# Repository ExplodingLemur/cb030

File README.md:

# cb030
4-layer redesign of the [CB030](https://www.retrobrewcomputers.org/doku.php?id=builderpages:plasmo:cb030) homebrew computer by plasmo on retrobrewcomputers.org.

Specifically based on the [16-bit CF interface variant rev1](https://www.retrobrewcomputers.org/doku.php?id=builderpages:plasmo:cb030:cb030_rev1:16-bit_cf_upgrade)

Requires [these KiCAD library files](https://github.com/ExplodingLemur/kicad_libs)

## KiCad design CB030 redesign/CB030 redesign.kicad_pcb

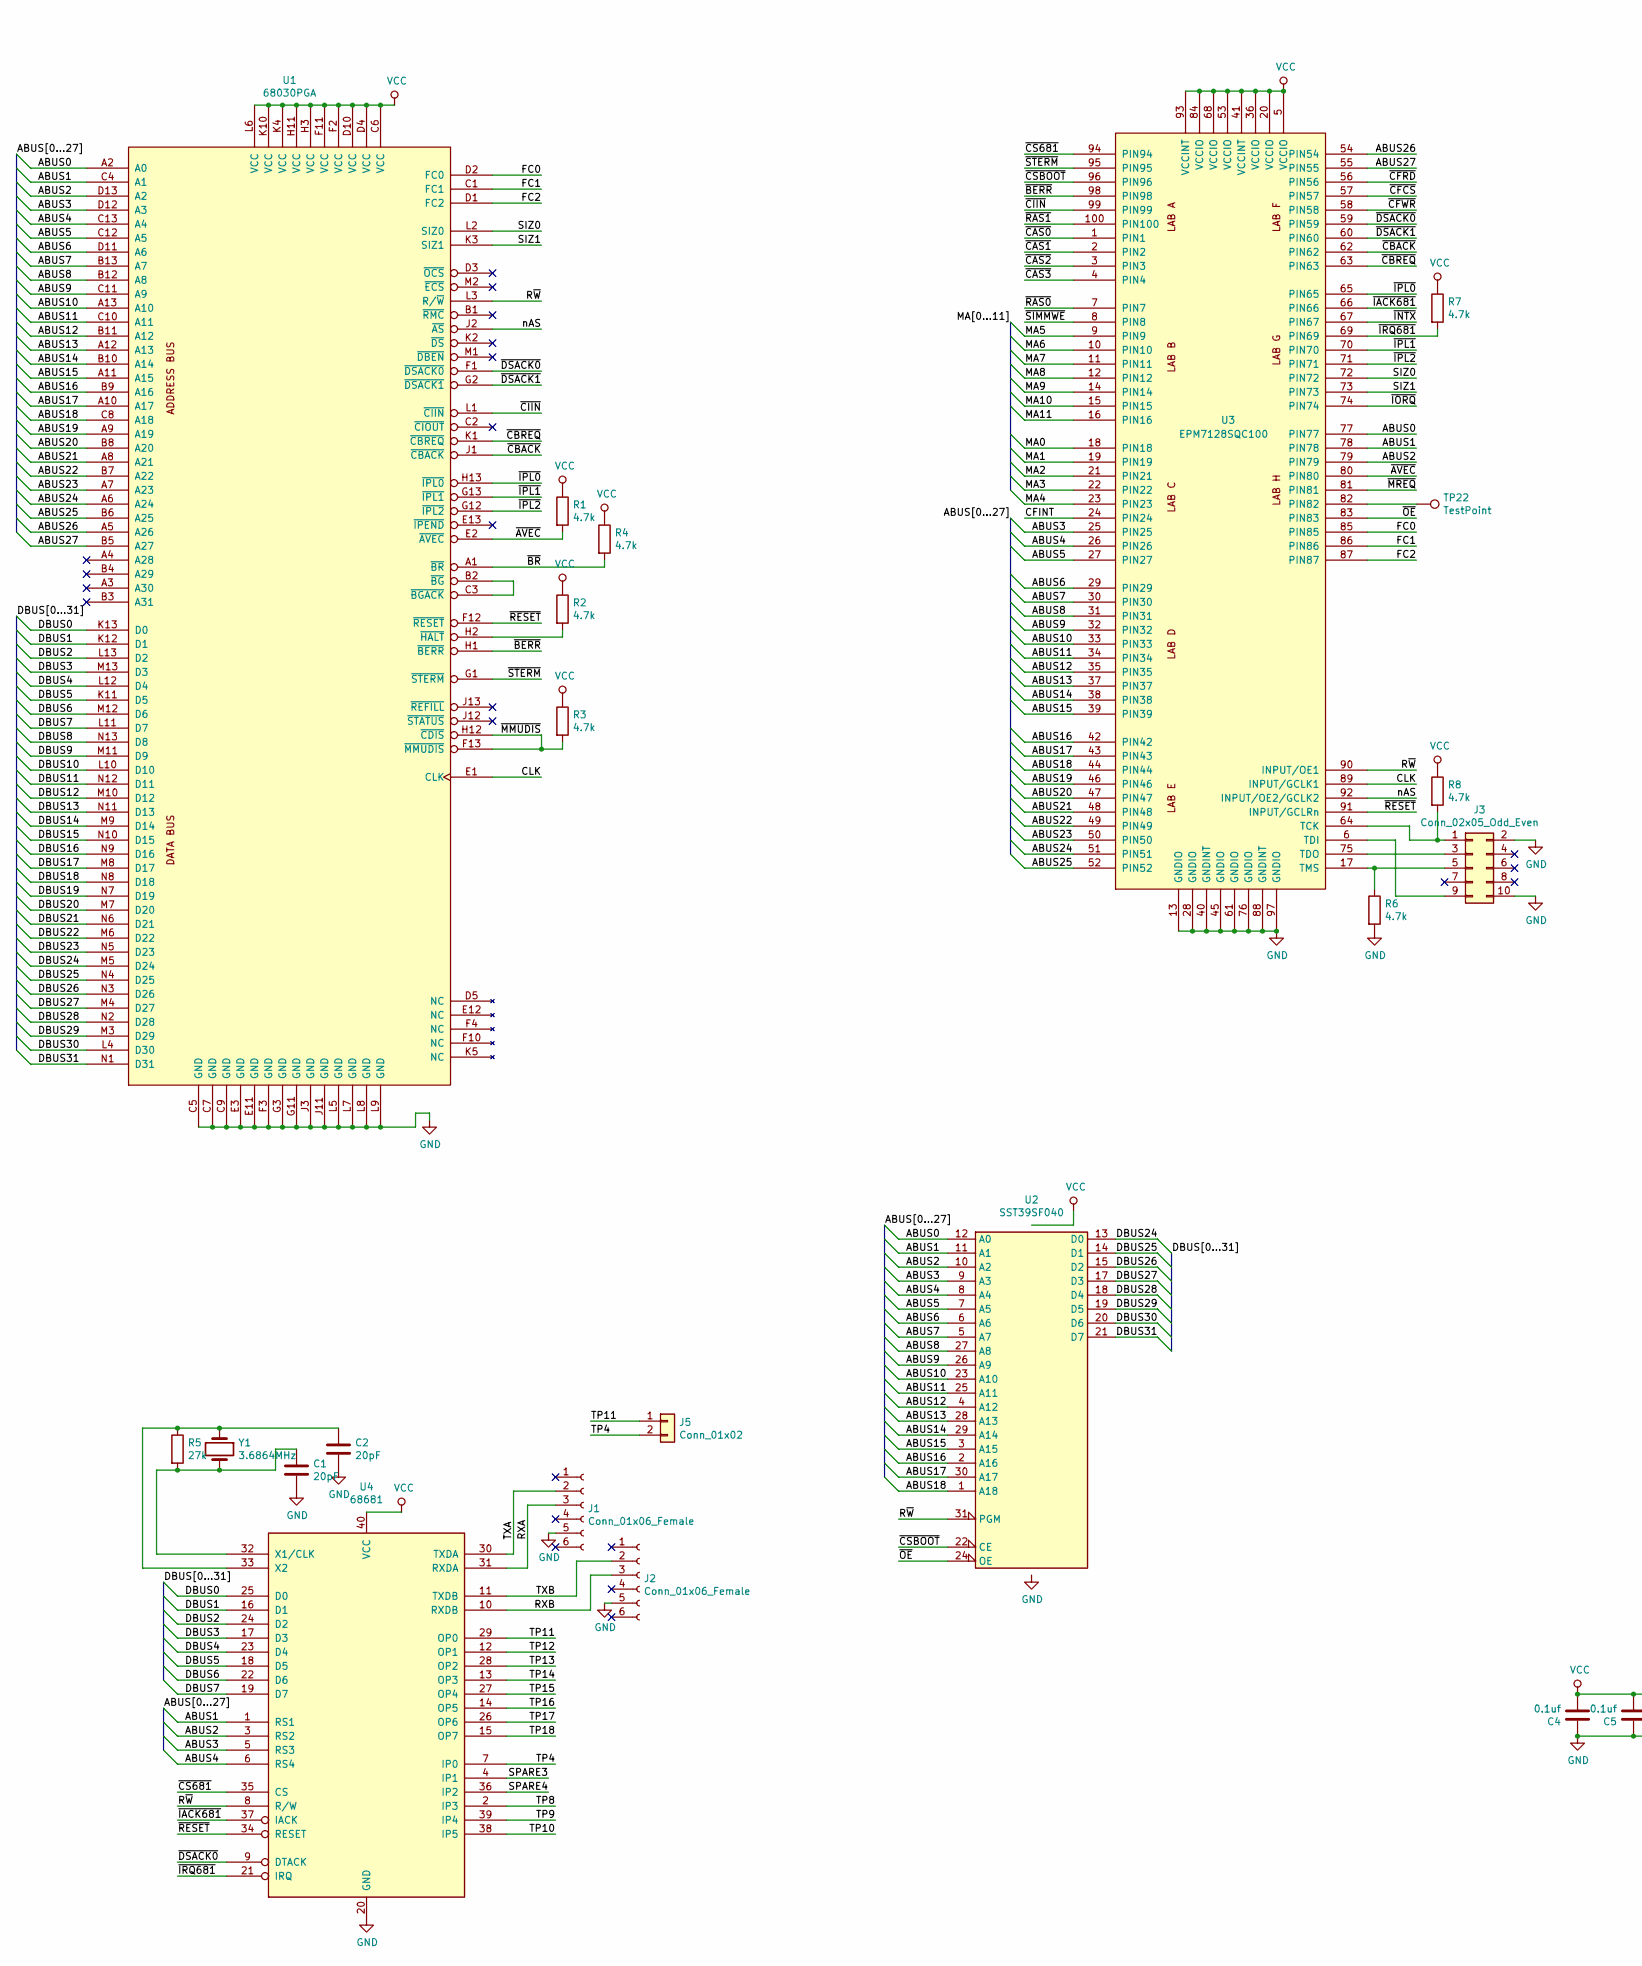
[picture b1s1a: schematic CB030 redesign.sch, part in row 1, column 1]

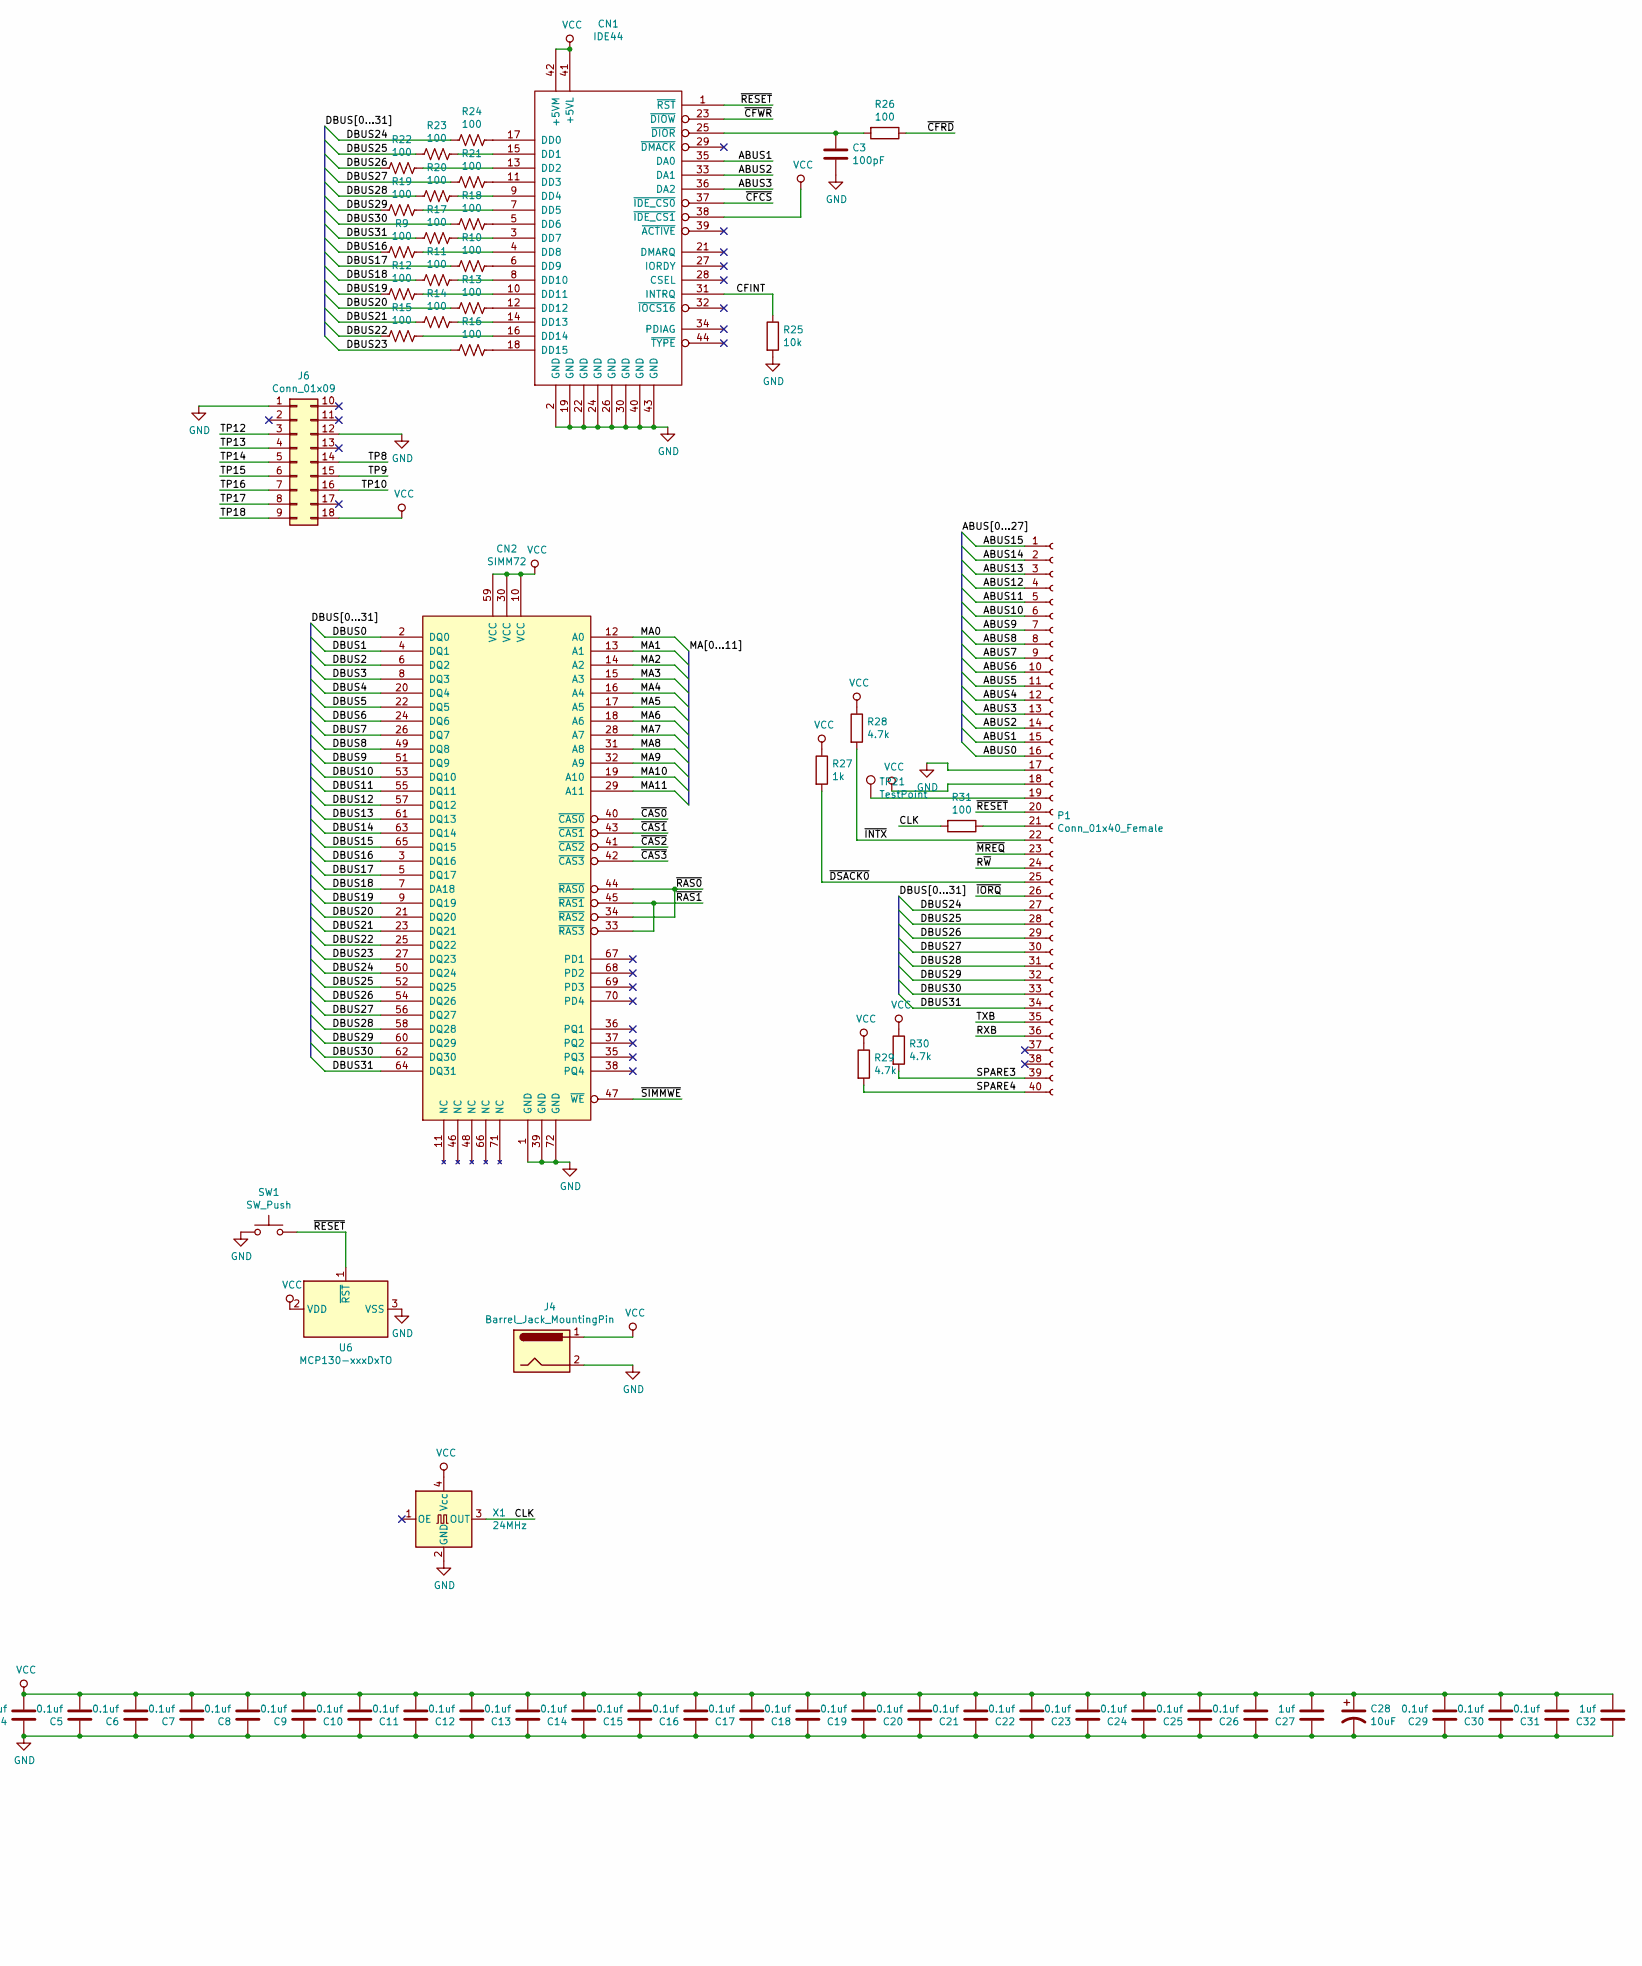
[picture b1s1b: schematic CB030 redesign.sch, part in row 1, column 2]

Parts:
C1, C2: 20pF; C_0805_2012Metric_Pad1.15x1.40mm_HandSolder
C3: 100pF; C_0805_2012Metric_Pad1.15x1.40mm_HandSolder
C4, C5, C6, C7, C8, C9, C10, C11, C12, C13, C14, C15, C16, C17, C18, C19, C20, C21, C22, C23, C24, C25, C26, C29, C30, C31: 0.1uf; C_0805_2012Metric_Pad1.15x1.40mm_HandSolder
C27, C32: 1uf; C_0805_2012Metric_Pad1.15x1.40mm_HandSolder
C28: 10uF; CP_Elec_4x5.8
CN1: IDE44; PinHeader_2x22_P2.00mm_Vertical
CN2: SIMM72; SIMM 72POS LEFT
J1: Conn_01x06_Female; PinSocket_1x06_P2.54mm_Vertical
J2: Conn_01x06_Female; PinSocket_1x06_P2.54mm_Horizontal
J3: Conn_02x05_Odd_Even; PinHeader_2x05_P2.54mm_Vertical
J4: Barrel_Jack_MountingPin; BarrelJack_Horizontal
J5: Conn_01x02; PinHeader_1x02_P2.54mm_Vertical
J6: Conn_01x09; PinHeader_2x09_P2.54mm_Vertical
P1: Conn_01x40_Female; PinSocket_1x40_P2.54mm_Vertical
R1, R2, R3, R4, R6, R7, R8, R28, R29, R30: 4.7k; R_0805_2012Metric_Pad1.15x1.40mm_HandSolder
R5: 27k; R_0805_2012Metric_Pad1.15x1.40mm_HandSolder
R9, R10, R11, R12, R13, R14, R15, R16, R17, R18, R19, R20, R21, R22, R23, R24, R26, R31: 100; R_0805_2012Metric_Pad1.15x1.40mm_HandSolder
R25: 10k; R_0805_2012Metric_Pad1.15x1.40mm_HandSolder
R27: 1k; R_0805_2012Metric_Pad1.15x1.40mm_HandSolder
SW1: SW_Push; SW_PUSH_6mm
TP21, TP22: TestPoint; TestPoint_THTPad_D1.5mm_Drill0.7mm
U1: 68030PGA; MC68030-RC
U2: SST39SF040; DIP-32_W15.24mm_Socket
U3: EPM7128SQC100; PQFP-100_14x20mm_P0.65mm
U4: 68681; DIP-40_W15.24mm_Socket
U6: MCP130-xxxDxTO; TO-92_Inline
X1: 24MHz; Oscillator_SMD_SeikoEpson_SG8002CA-4Pin_7.0x5.0mm_HandSolde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; Part SG7050CCN 24.000000M-HJGA3
Y1: 3.6864MHz; Crystal_SMD_HC49-SD_HandSoldering; Part ABLS-3.6864MHZ-20-B-3-H-T

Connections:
/ABUS0: P1.16, U1.A2 (A0), U2.12 (A0), U3.77 (PIN77)
/ABUS1: CN1.35 (DA0), P1.15, U1.C4 (A1), U2.11 (A1), U3.78 (PIN78), U4.1 (RS1)
/ABUS2: CN1.33 (DA1), P1.14, U1.D13 (A2), U2.10 (A2), U3.79 (PIN79), U4.3 (RS2)
/ABUS3: CN1.36 (DA2), P1.13, U1.D12 (A3), U2.9 (A3), U3.25 (PIN25), U4.5 (RS3)
/ABUS4: P1.12, U1.C13 (A4), U2.8 (A4), U3.26 (PIN26), U4.6 (RS4)
/ABUS5: P1.11, U1.C12 (A5), U2.7 (A5), U3.27 (PIN27)
/ABUS6: P1.10, U1.D11 (A6), U2.6 (A6), U3.29 (PIN29)
/ABUS7: P1.9, U1.B13 (A7), U2.5 (A7), U3.30 (PIN30)
/ABUS8: P1.8, U1.B12 (A8), U2.27 (A8), U3.31 (PIN31)
/ABUS9: P1.7, U1.C11 (A9), U2.26 (A9), U3.32 (PIN32)
/ABUS10: P1.6, U1.A13 (A10), U2.23 (A10), U3.33 (PIN33)
/ABUS11: P1.5, U1.C10 (A11), U2.25 (A11), U3.34 (PIN34)
/ABUS12: P1.4, U1.B11 (A12), U2.4 (A12), U3.35 (PIN35)
/ABUS13: P1.3, U1.A12 (A13), U2.28 (A13), U3.37 (PIN37)
/ABUS14: P1.2, U1.B10 (A14), U2.29 (A14), U3.38 (PIN38)
/ABUS15: P1.1, U1.A11 (A15), U2.3 (A15), U3.39 (PIN39)
/ABUS16: U1.B9 (A16), U2.2 (A16), U3.42 (PIN42)
/ABUS17: U1.A10 (A17), U2.30 (A17), U3.43 (PIN43)
/ABUS18: U1.C8 (A18), U2.1 (A18), U3.44 (PIN44)
/ABUS19: U1.A9 (A19), U3.46 (PIN46)
/ABUS20: U1.B8 (A20), U3.47 (PIN47)
/ABUS21: U1.A8 (A21), U3.48 (PIN48)
/ABUS22: U1.B7 (A22), U3.49 (PIN49)
/ABUS23: U1.A7 (A23), U3.50 (PIN50)
/ABUS24: U1.A6 (A24), U3.51 (PIN51)
/ABUS25: U1.B6 (A25), U3.52 (PIN52)
/ABUS26: U1.A5 (A26), U3.54 (PIN54)
/ABUS27: U1.B5 (A27), U3.55 (PIN55)
/CFINT: CN1.31 (INTRQ), R25.1, U3.24 (PIN24)
/CLK: R31.2, U1.E1 (CLK), U3.89 (INPUT/GCLK1), X1.3 (OUT)
/DBUS0: CN2.2 (DQ0), U1.K13 (D0), U4.25 (D0)
/DBUS1: CN2.4 (DQ1), U1.K12 (D1), U4.16 (D1)
/DBUS2: CN2.6 (DQ2), U1.L13 (D2), U4.24 (D2)
/DBUS3: CN2.8 (DQ3), U1.M13 (D3), U4.17 (D3)
/DBUS4: CN2.20 (DQ4), U1.L12 (D4), U4.23 (D4)
/DBUS5: CN2.22 (DQ5), U1.K11 (D5), U4.18 (D5)
/DBUS6: CN2.24 (DQ6), U1.M12 (D6), U4.22 (D6)
/DBUS7: CN2.26 (DQ7), U1.L11 (D7), U4.19 (D7)
/DBUS8: CN2.49 (DQ8), U1.N13 (D8)
/DBUS9: CN2.51 (DQ9), U1.M11 (D9)
/DBUS10: CN2.53 (DQ10), U1.L10 (D10)
/DBUS11: CN2.55 (DQ11), U1.N12 (D11)
/DBUS12: CN2.57 (DQ12), U1.M10 (D12)
/DBUS13: CN2.61 (DQ13), U1.N11 (D13)
/DBUS14: CN2.63 (DQ14), U1.M9 (D14)
/DBUS15: CN2.65 (DQ15), U1.N10 (D15)
/DBUS16: CN2.3 (DQ16), R9.2, U1.N9 (D16)
/DBUS17: CN2.5 (DQ17), R10.2, U1.M8 (D17)
/DBUS18: CN2.7 (DA18), R11.2, U1.N8 (D18)
/DBUS19: CN2.9 (DQ19), R12.2, U1.N7 (D19)
/DBUS20: CN2.21 (DQ20), R13.2, U1.M7 (D20)
/DBUS21: CN2.23 (DQ21), R14.2, U1.N6 (D21)
/DBUS22: CN2.25 (DQ22), R15.2, U1.M6 (D22)
/DBUS23: CN2.27 (DQ23), R16.2, U1.N5 (D23)
/DBUS24: CN2.50 (DQ24), P1.27, R24.2, U1.M5 (D24), U2.13 (D0)
/DBUS25: CN2.52 (DQ25), P1.28, R23.2, U1.N4 (D25), U2.14 (D1)
/DBUS26: CN2.54 (DQ26), P1.29, R22.2, U1.N3 (D26), U2.15 (D2)
/DBUS27: CN2.56 (DQ27), P1.30, R21.2, U1.M4 (D27), U2.17 (D3)
/DBUS28: CN2.58 (DQ28), P1.31, R20.2, U1.N2 (D28), U2.18 (D4)
/DBUS29: CN2.60 (DQ29), P1.32, R19.2, U1.M3 (D29), U2.19 (D5)
/DBUS30: CN2.62 (DQ30), P1.33, R18.2, U1.L4 (D30), U2.20 (D6)
/DBUS31: CN2.64 (DQ31), P1.34, R17.2, U1.N1 (D31), U2.21 (D7)
/FC0: U1.D2 (FC0), U3.85 (PIN85)
/FC1: U1.C1 (FC1), U3.86 (PIN86)
/FC2: U1.D1 (FC2), U3.87 (PIN87)
/MA0: CN2.12 (A0), U3.18 (PIN18)
/MA1: CN2.13 (A1), U3.19 (PIN19)
/MA2: CN2.14 (A2), U3.21 (PIN21)
/MA3: CN2.15 (A3), U3.22 (PIN22)
/MA4: CN2.16 (A4), U3.23 (PIN23)
/MA5: CN2.17 (A5), U3.9 (PIN9)
/MA6: CN2.18 (A6), U3.10 (PIN10)
/MA7: CN2.28 (A7), U3.11 (PIN11)
/MA8: CN2.31 (A8), U3.12 (PIN12)
/MA9: CN2.32 (A9), U3.14 (PIN14)
/MA10: CN2.19 (A10), U3.15 (PIN15)
/MA11: CN2.29 (A11), U3.16 (PIN16)
/RXA: J1.3, U4.31 (RXDA)
/RXB: J2.3, P1.36, U4.10 (RXDB)
/R~W: P1.24, U1.L3 (R/~W), U2.31 (PGM), U3.90 (INPUT/OE1), U4.8 (R/W)
/SIZ0: U1.L2 (SIZ0), U3.72 (PIN72)
/SIZ1: U1.K3 (SIZ1), U3.73 (PIN73)
/SPARE3: P1.39, R30.2, U4.4 (IP1)
/SPARE4: P1.40, R29.2, U4.36 (IP2)
/TP4: J5.2, U4.7 (IP0)
/TP8: J6.14, U4.2 (IP3)
/TP9: J6.15, U4.39 (IP4)
/TP10: J6.16, U4.38 (IP5)
/TP11: J5.1, U4.29 (OP0)
/TP12: J6.3, U4.12 (OP1)
/TP13: J6.4, U4.28 (OP2)
/TP14: J6.5, U4.13 (OP3)
/TP15: J6.6, U4.27 (OP4)
/TP16: J6.7, U4.14 (OP5)
/TP17: J6.8, U4.26 (OP6)
/TP18: J6.9, U4.15 (OP7)
/TXA: J1.2, U4.30 (TXDA)
/TXB: J2.2, P1.35, U4.11 (TXDB)
/nAS: U1.J2 (~AS), U3.92 (INPUT/OE2/GCLK2)
/~AVEC: R1.2, U1.E2 (~AVEC), U3.80 (PIN80)
/~BERR: U1.H1 (~BERR), U3.98 (PIN98)
/~BR: R4.2, U1.A1 (~BR)
/~CAS0: CN2.40 (~CAS0), U3.1 (PIN1)
/~CAS1: CN2.43 (~CAS1), U3.2 (PIN2)
/~CAS2: CN2.41 (~CAS2), U3.3 (PIN3)
/~CAS3: CN2.42 (~CAS3), U3.4 (PIN4)
/~CBACK: U1.J1 (~CBACK), U3.62 (PIN62)
/~CBREQ: U1.K1 (~CBREQ), U3.63 (PIN63)
/~CFCS: CN1.37 (~IDE_CS0), U3.57 (PIN57)
/~CFRD: R26.1, U3.56 (PIN56)
/~CFWR: CN1.23 (~DIOW), U3.58 (PIN58)
/~CIIN: U1.L1 (~CIIN), U3.99 (PIN99)
/~CS681: U3.94 (PIN94), U4.35 (CS)
/~CSBOOT: U2.22 (CE), U3.96 (PIN96)
/~DSACK0: P1.25, R27.2, U1.F1 (~DSACK0), U3.59 (PIN59), U4.9 (DTACK)
/~DSACK1: U1.G2 (~DSACK1), U3.60 (PIN60)
/~IACK681: U3.66 (PIN66), U4.37 (IACK)
/~INTX: P1.22, R28.2, U3.67 (PIN67)
/~IORQ: P1.26, U3.74 (PIN74)
/~IPL0: U1.H13 (~IPL0), U3.65 (PIN65)
/~IPL1: U1.G13 (~IPL1), U3.70 (PIN70)
/~IPL2: U1.G12 (~IPL2), U3.71 (PIN71)
/~IRQ681: R7.2, U3.69 (PIN69), U4.21 (IRQ)
/~MMUDIS: R3.2, U1.F13 (~MMUDIS), U1.H12 (~CDIS)
/~MREQ: P1.23, U3.81 (PIN81)
/~OE: U2.24 (OE), U3.83 (PIN83)
/~RAS0: CN2.34 (~RAS2), CN2.44 (~RAS0), U3.7 (PIN7)
/~RAS1: CN2.33 (~RAS3), CN2.45 (~RAS1), U3.100 (PIN100)
/~RESET: CN1.1 (~RST), P1.20, SW1.2, U1.F12 (~RESET), U3.91 (INPUT/GCLRn), U4.34 (RESET), U6.1 (~RST)
/~SIMMWE: CN2.47 (~WE), U3.8 (PIN8)
/~STERM: U1.G1 (~STERM), U3.95 (PIN95)
GND: C1.2, C2.2, C3.2, C4.1, C5.1, C6.1, C7.1, C8.1, C9.1, C10.1, C11.1, C12.1, C13.1, C14.1, C15.1, C16.1, C17.1, C18.1, C19.1, C20.1, C21.1, C22.1, C23.1, C24.1, C25.1, C26.1, C27.1, C28.2, C29.1, C30.1, C31.1, C32.1, CN1.2 (GND), CN1.19 (GND), CN1.22 (GND), CN1.24 (GND), CN1.26 (GND), CN1.30 (GND), CN1.40 (GND), CN1.43 (GND), CN2.1 (GND), CN2.39 (GND), CN2.72 (GND), J1.5, J2.5, J3.2, J3.10, J4.2, J6.1, J6.12, P1.17, R6.2, R25.2, SW1.1, U1.C5 (GND), U1.C7 (GND), U1.C9 (GND), U1.E3 (GND), U1.E11 (GND), U1.F3 (GND), U1.G3 (GND), U1.G11 (GND), U1.J3 (GND), U1.J11 (GND), U1.L5 (GND), U1.L7 (GND), U1.L8 (GND), U1.L9 (GND), U2.16 (GND), U3.13 (GNDIO), U3.28 (GNDIO), U3.40 (GNDINT), U3.45 (GNDIO), U3.61 (GNDIO), U3.76 (GNDIO), U3.88 (GNDINT), U3.97 (GNDIO), U4.20 (GND), U6.3 (VSS), X1.2 (GND)
unnamed: C1.1, R5.2, U4.32 (X1/CLK), Y1.2
unnamed: C2.1, R5.1, U4.33 (X2), Y1.1
unnamed: C3.1, CN1.25 (~DIOR), R26.2
unnamed: CN1.3 (DD7), R17.1
unnamed: CN1.4 (DD8), R9.1
unnamed: CN1.5 (DD6), R18.1
unnamed: CN1.6 (DD9), R10.1
unnamed: CN1.7 (DD5), R19.1
unnamed: CN1.8 (DD10), R11.1
unnamed: CN1.9 (DD4), R20.1
unnamed: CN1.10 (DD11), R12.1
unnamed: CN1.11 (DD3), R21.1
unnamed: CN1.12 (DD12), R13.1
unnamed: CN1.13 (DD2), R22.1
unnamed: CN1.14 (DD13), R14.1
unnamed: CN1.15 (DD1), R23.1
unnamed: CN1.16 (DD14), R15.1
unnamed: CN1.17 (DD0), R24.1
unnamed: CN1.18 (DD15), R16.1
unnamed: J3.1, R8.2, U3.64 (TCK)
unnamed: J3.3, U3.75 (TDO)
unnamed: J3.5, R6.1, U3.17 (TMS)
unnamed: J3.9, U3.6 (TDI)
unnamed: P1.19, TP21.1
unnamed: P1.21, R31.1
unnamed: R2.2, U1.H2 (~HALT)
unnamed: TP22.1, U3.82 (PIN82)
unnamed: U1.B2 (~BG), U1.C3 (~BGACK)
VCC: C4.2, C5.2, C6.2, C7.2, C8.2, C9.2, C10.2, C11.2, C12.2, C13.2, C14.2, C15.2, C16.2, C17.2, C18.2, C19.2, C20.2, C21.2, C22.2, C23.2, C24.2, C25.2, C26.2, C27.2, C28.1, C29.2, C30.2, C31.2, C32.2, CN1.38 (~IDE_CS1), CN1.41 (+5VL), CN1.42 (+5VM), CN2.10 (VCC), CN2.30 (VCC), CN2.59 (VCC), J4.1, J6.18, P1.18, R1.1, R2.1, R3.1, R4.1, R7.1, R8.1, R27.1, R28.1, R29.1, R30.1, U1.C6 (VCC), U1.D4 (VCC), U1.D10 (VCC), U1.F2 (VCC), U1.F11 (VCC), U1.H3 (VCC), U1.H11 (VCC), U1.K4 (VCC), U1.K10 (VCC), U1.L6 (VCC), U2.32 (VCC), U3.5 (VCCIO), U3.20 (VCCIO), U3.36 (VCCIO), U3.41 (VCCINT), U3.53 (VCCIO), U3.68 (VCCIO), U3.84 (VCCIO), U3.93 (VCCINT), U4.40 (VCC), U6.2 (VDD), X1.4 (Vcc)

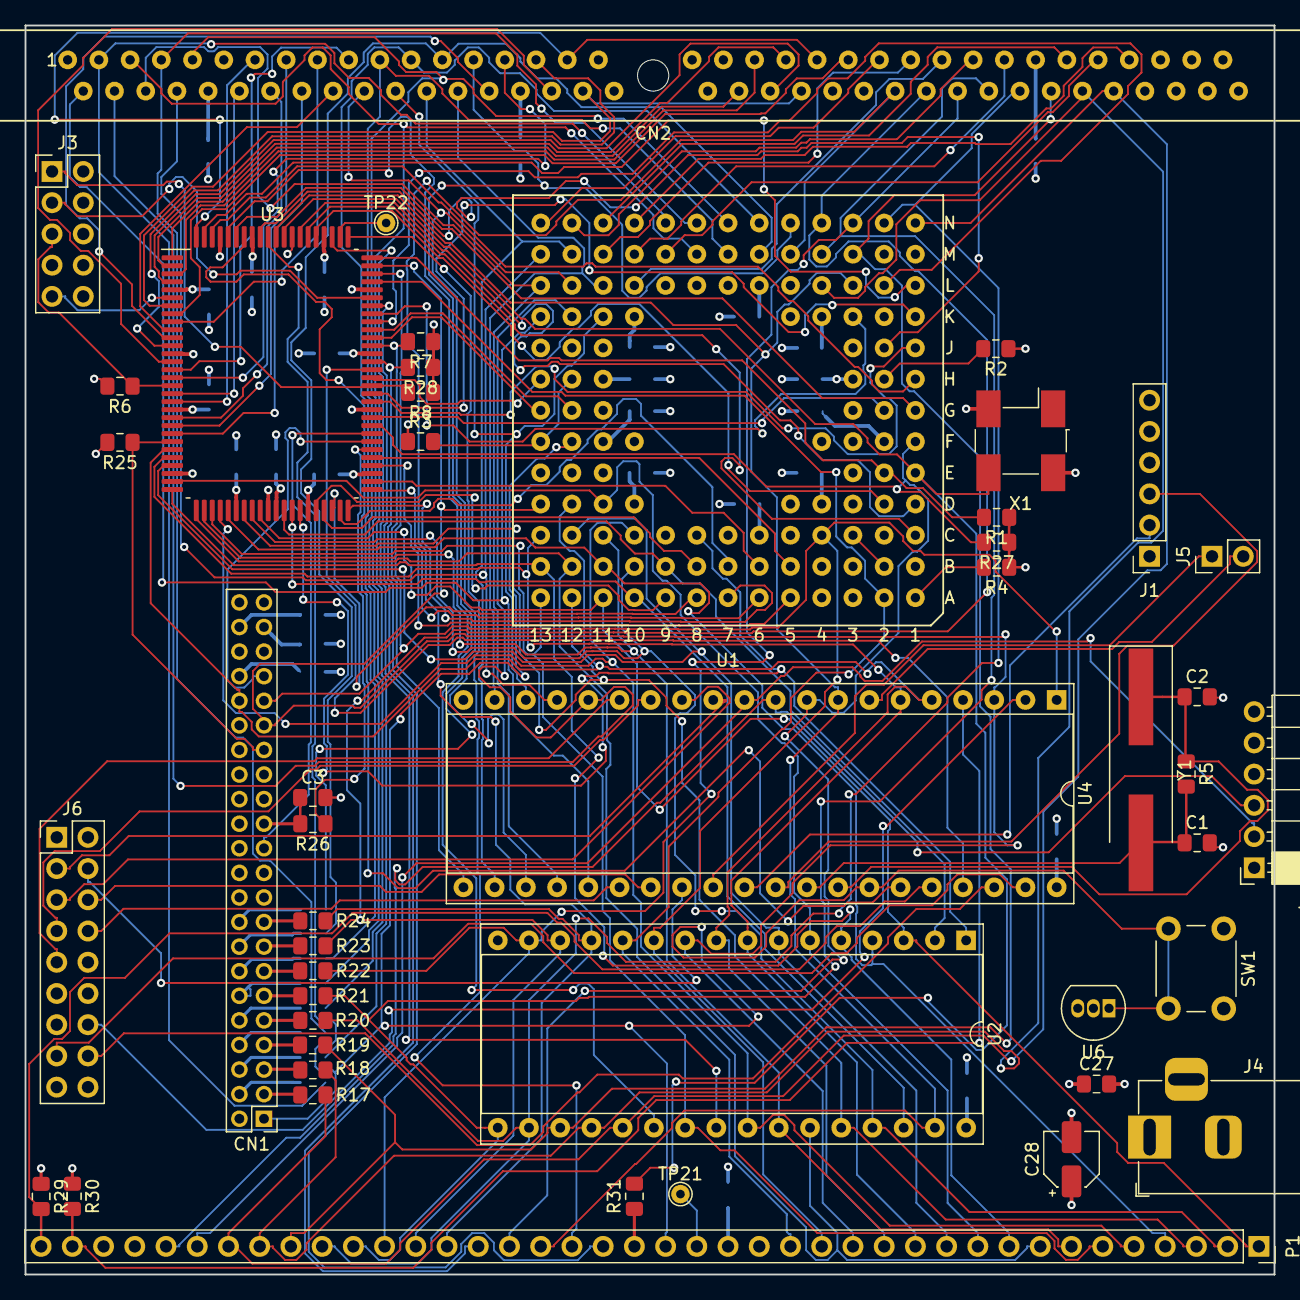
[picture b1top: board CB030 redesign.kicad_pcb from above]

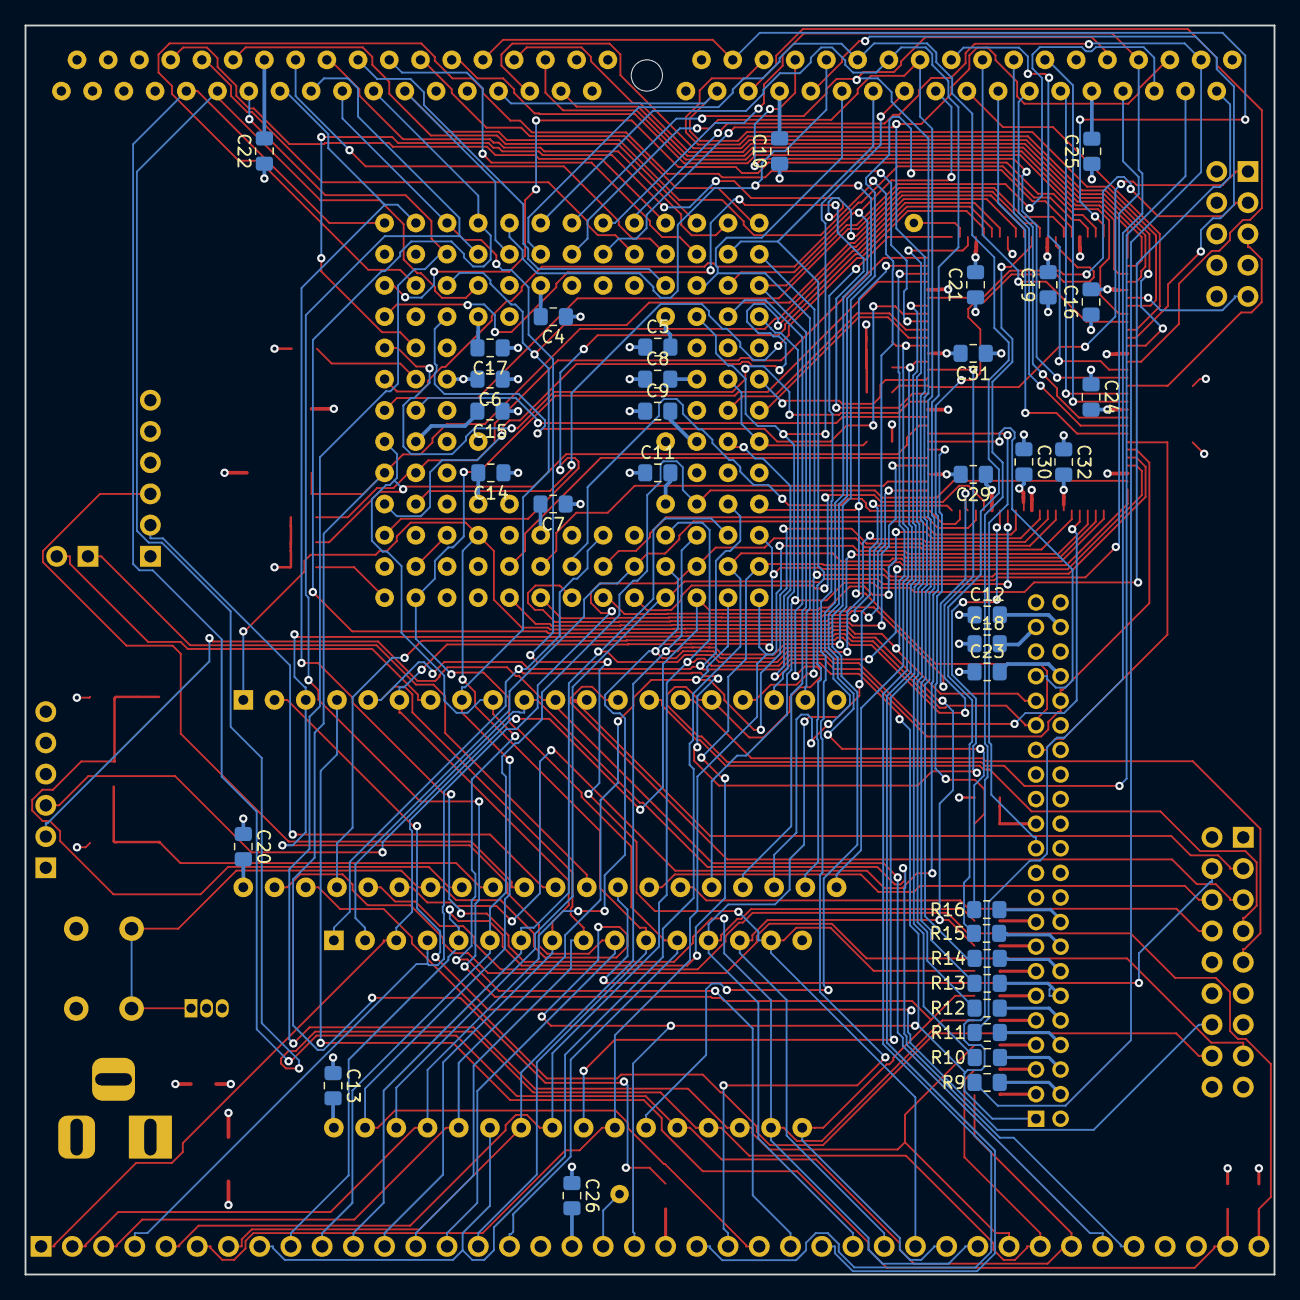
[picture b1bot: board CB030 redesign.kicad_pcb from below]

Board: 4 copper layers, 101.6 x 101.6 mm, 82 parts (35 on the bottom side), 161 nets.

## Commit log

2020-06-22 First rev
    First revision, sent to board house.
